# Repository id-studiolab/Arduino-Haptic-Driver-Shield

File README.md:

##Arduino Haptic Driver Shield 

Arduino shield containing four TI 2605 haptic driver ICs.

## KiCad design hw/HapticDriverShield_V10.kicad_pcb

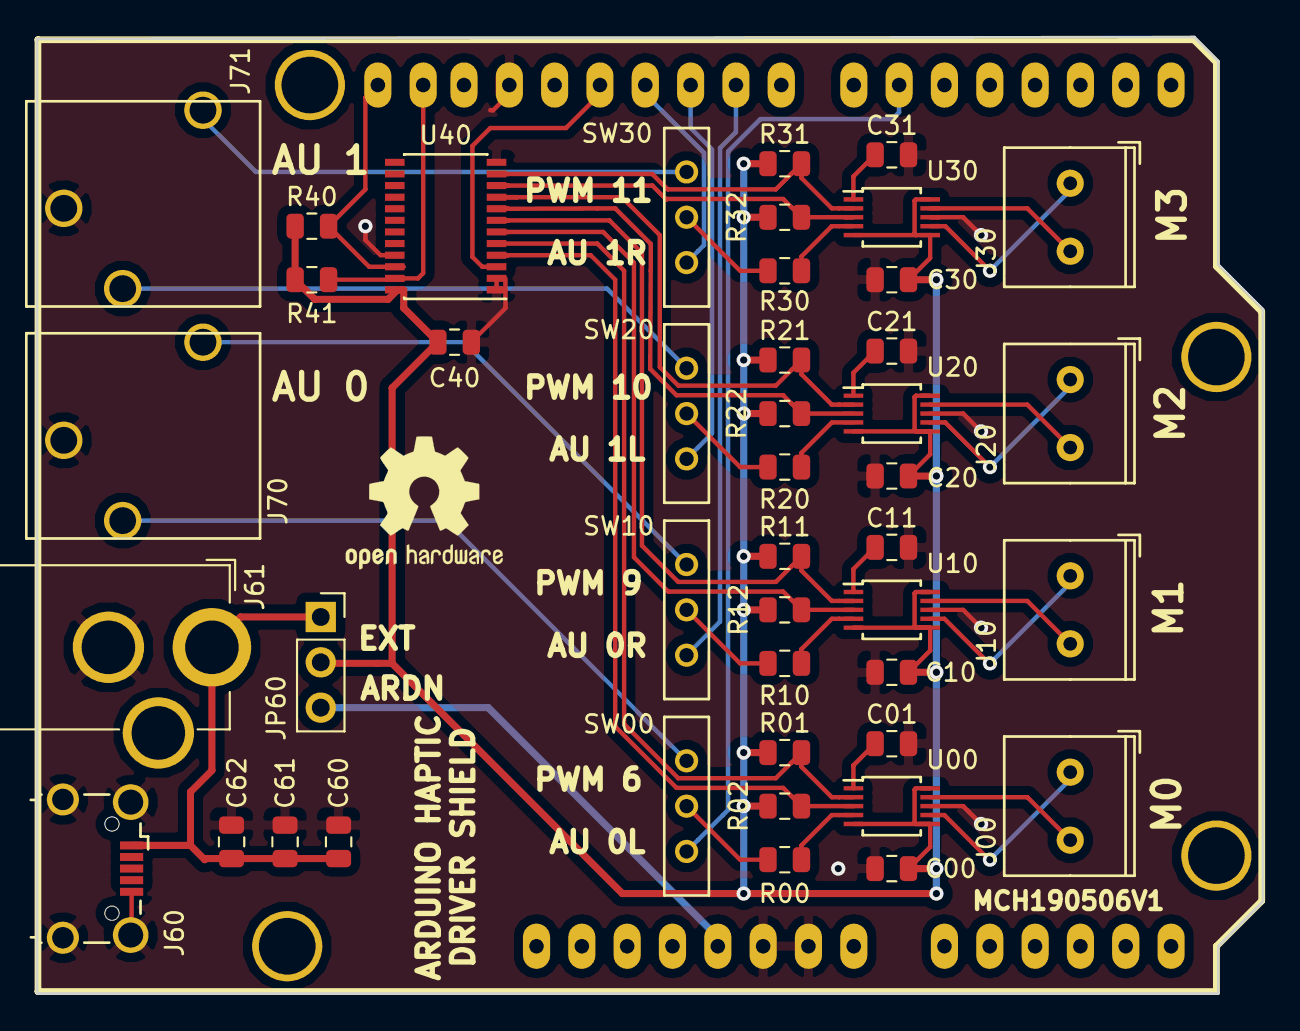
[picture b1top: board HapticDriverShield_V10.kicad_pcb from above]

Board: 2 copper layers, 68.7 x 53.6 mm, 45 parts (0 on the bottom side), 43 nets.

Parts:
C00, C01, C10, C11, C20, C21, C30, C31, C61: 1uF; C_0805_2012Metric
C40, C60: 100nF; C_0805_2012Metric
C62: 10uF; C_0805_2012Metric
J00, J10, J20, J30: Conn_01x02; Phoenix_MKDS_2P_3.81
J60: USB_B_Micro; USB_Micro-B_Wuerth_629105150521_CircularHoles
J61: Jack-DC; BarrelJack_Wuerth_6941xx301002
J70, J71: AudioJack3_Ground; MJ-352W-0
JP60: Jumper_NC_Dual; PinSocket_1x03_P2.54mm_Vertical
R00, R10, R20, R30: 1K; R_0805_2012Metric
R01, R02, R11, R12, R21, R22, R31, R32, R40, R41: 4K7; R_0805_2012Metric
SHIELD00: ARDUINO_SHIELD
SW00, SW10, SW20, SW30: 450301014042; WUERTH-450301014042-ND
U00, U10, U20, U30: DRV2605L; TSSOP-10_3x3mm_P0.5mm
U40: TCA9548APWR; TSSOP-24_4.4x7.8mm_P0.65mm

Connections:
5V: JP60.3, SHIELD00.5V
AUDIO0-L: J70.T, SW00.3
AUDIO0-R: J70.R, SW10.3
AUDIO1-L: J71.T, SW20.3
AUDIO1-R: J71.R, SW30.3
GND: C00.1, C01.2, C10.1, C11.2, C20.1, C21.2, C30.1, C31.2, C40.2, C60.2, C61.2, C62.2, J60.5, J60.6, J61.2, J70.S, J71.S, SHIELD00.GND1, SHIELD00.GND2, SHIELD00.GND3, U00.8, U10.8, U20.8, U30.8, U40.1, U40.2, U40.12, U40.21
IO6: SHIELD00.6, SW00.2
IO9: SHIELD00.9, SW10.2
IO10: SHIELD00.10, SW20.2
IO11: SHIELD00.11, SW30.2
IO12: SHIELD00.12, U40.3
unnamed: C01.1, U00.1
unnamed: C11.1, U10.1
unnamed: C21.1, U20.1
unnamed: C31.1, U30.1
unnamed: C60.1, C61.1, C62.1, J60.1, J61.1, JP60.1
unnamed: J00.1, U00.7
unnamed: J00.2, U00.9
unnamed: J10.1, U10.7
unnamed: J10.2, U10.9
unnamed: J20.1, U20.7
unnamed: J20.2, U20.9
unnamed: J30.1, U30.7
unnamed: J30.2, U30.9
unnamed: R00.1, SW00.1
unnamed: R00.2, U00.4
unnamed: R10.1, SW10.1
unnamed: R10.2, U10.4
unnamed: R20.1, SW20.1
unnamed: R20.2, U20.4
unnamed: R30.1, SW30.1
unnamed: R30.2, U30.4
SC0: R01.2, U00.2, U40.5
SC1: R11.2, U10.2, U40.7
SC2: R21.2, U20.2, U40.9
SC3: R31.2, U30.2, U40.11
SCL: R40.2, SHIELD00.SCL, U40.22
SD0: R02.2, U00.3, U40.4
SD1: R12.2, U10.3, U40.6
SD2: R22.2, U20.3, U40.8
SD3: R32.2, U30.3, U40.10
SDA: R41.2, SHIELD00.SDA, U40.23
VDD: C00.2, C10.2, C20.2, C30.2, C40.1, JP60.2, R01.1, R02.1, R11.1, R12.1, R21.1, R22.1, R31.1, R32.1, R40.1, R41.1, U00.5, U00.6, U00.10, U10.5, U10.6, U10.10, U20.5, U20.6, U20.10, U30.5, U30.6, U30.10, U40.24

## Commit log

2019-05-01 First push
2019-05-01 hardware added
2019-05-15 hw v1.0
